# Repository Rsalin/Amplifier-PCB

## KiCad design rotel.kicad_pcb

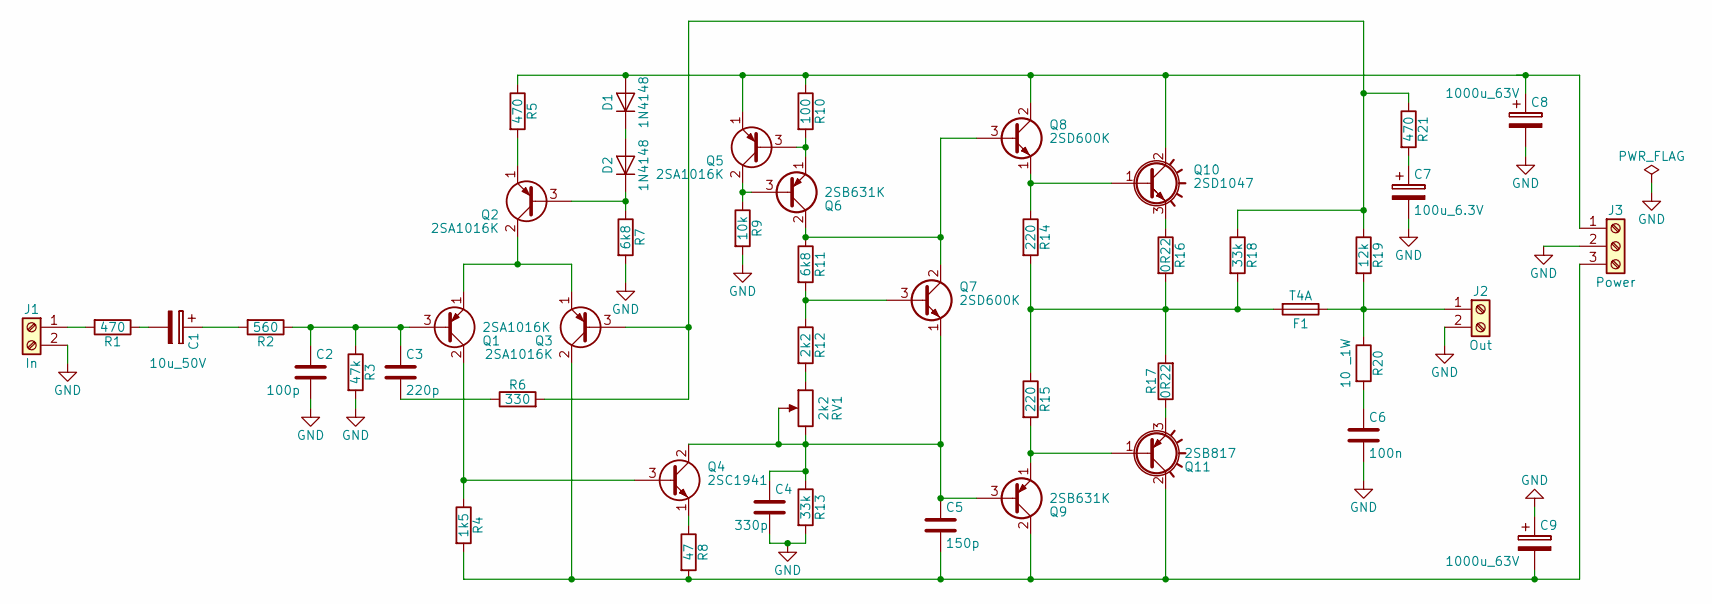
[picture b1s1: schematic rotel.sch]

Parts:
C1: 10u_50V; CP_Radial_D8.0mm_P3.80mm
C2: 100p; C_Rect_L7.0mm_W2.5mm_P5.00mm
C3: 220p; C_Rect_L7.0mm_W2.5mm_P5.00mm
C4: 330p; C_Rect_L7.0mm_W2.5mm_P5.00mm
C5: 150p; C_Rect_L7.0mm_W2.5mm_P5.00mm
C6: 100n; C_Rect_L7.0mm_W2.5mm_P5.00mm
C7: 100u_6.3V; CP_Radial_D8.0mm_P3.80mm
C8, C9: 1000u_63V; CP_Radial_D18.0mm_P7.50mm
D1, D2: 1N4148; D_DO-35_SOD27_P10.16mm_Horizontal
F1: T4A; Fuseholder5x20_horiz_SemiClosed_Casing10x25mm
J1: In; TerminalBlock_Phoenix_MKDS1.5-2pol
J2: Out; TerminalBlock_Phoenix_MKDS1.5-2pol
J3: Power; TerminalBlock_Phoenix_MKDS1.5-3pol
Q1, Q2, Q3, Q5: 2SA1016K; TO-92_Inline_Narrow_Oval
Q4: 2SC1941; TO-92_Inline_Narrow_Oval
Q6, Q9: 2SB631K; TO-126_Vertical
Q7, Q8: 2SD600K; TO-126_Vertical
Q10: 2SD1047; TO-247_TO-3P_Vertical
Q11: 2SB817; TO-247_TO-3P_Vertical
R1, R5, R21: 470; R_Axial_DIN0207_L6.3mm_D2.5mm_P10.16mm_Horizontal
R2: 560; R_Axial_DIN0207_L6.3mm_D2.5mm_P10.16mm_Horizontal
R3: 47k; R_Axial_DIN0207_L6.3mm_D2.5mm_P10.16mm_Horizontal
R4: 1k5; R_Axial_DIN0207_L6.3mm_D2.5mm_P10.16mm_Horizontal
R6: 330; R_Axial_DIN0207_L6.3mm_D2.5mm_P10.16mm_Horizontal
R7, R11: 6k8; R_Axial_DIN0207_L6.3mm_D2.5mm_P10.16mm_Horizontal
R8: 47; R_Axial_DIN0207_L6.3mm_D2.5mm_P10.16mm_Horizontal
R9: 10k; R_Axial_DIN0207_L6.3mm_D2.5mm_P10.16mm_Horizontal
R10: 100; R_Axial_DIN0207_L6.3mm_D2.5mm_P10.16mm_Horizontal
R12: 2k2; R_Axial_DIN0207_L6.3mm_D2.5mm_P10.16mm_Horizontal
R13, R18: 33k; R_Axial_DIN0207_L6.3mm_D2.5mm_P10.16mm_Horizontal
R14, R15: 220; R_Axial_DIN0207_L6.3mm_D2.5mm_P10.16mm_Horizontal
R16, R17: 0R22; R_Axial_Power_L20.0mm_W6.4mm_P7.62mm_Vertical
R19: 12k; R_Axial_DIN0207_L6.3mm_D2.5mm_P10.16mm_Horizontal
R20: 10 _1W; R_Axial_DIN0411_L9.9mm_D3.6mm_P15.24mm_Horizontal
RV1: 2k2; Potentiometer_Trimmer_ACP_CA9v_Horizontal_Px10.0mm_Py5.0mm

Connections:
GND: C2.2, C4.2, C6.2, C7.2, C8.2, C9.1, J1.2, J2.2, J3.2, R3.2, R7.2, R9.2, R13.2
unnamed: C1.1, R2.2
unnamed: C1.2, R1.1
unnamed: C2.1, C3.1, Q1.3 (B), R2.1, R3.1
unnamed: C3.2, R6.1
unnamed: C4.1, C5.1, Q4.2 (C), Q7.1 (E), Q9.3 (B), R13.1, RV1.2, RV1.3
unnamed: C5.2, C9.2, J3.3, Q3.2 (C), Q9.2 (C), Q11.2 (C), R4.2, R8.2
unnamed: C6.1, R20.2
unnamed: C7.1, R21.2
unnamed: C8.1, D1.2 (A), J3.1, Q5.1 (E), Q8.2 (C), Q10.2 (C), R5.1, R10.1
unnamed: D1.1 (K), D2.2 (A)
unnamed: D2.1 (K), Q2.3 (B), R7.1
unnamed: F1.1, J2.1, R19.2, R20.1
unnamed: F1.2, R14.2, R15.1, R16.2, R17.2, R18.2
unnamed: J1.1, R1.2
unnamed: Q1.1 (E), Q2.2 (C), Q3.1 (E)
unnamed: Q1.2 (C), Q4.3 (B), R4.1
unnamed: Q2.1 (E), R5.2
unnamed: Q3.3 (B), R6.2, R18.1, R19.1, R21.1
unnamed: Q4.1 (E), R8.1
unnamed: Q5.2 (C), Q6.3 (B), R9.1
unnamed: Q5.3 (B), Q6.1 (E), R10.2
unnamed: Q6.2 (C), Q7.2 (C), Q8.3 (B), R11.1
unnamed: Q7.3 (B), R11.2, R12.1
unnamed: Q8.1 (E), Q10.1 (B), R14.1
unnamed: Q10.3 (E), R16.1
unnamed: Q9.1 (E), Q11.1 (B), R15.2
unnamed: Q11.3 (E), R17.1
unnamed: R12.2, RV1.1

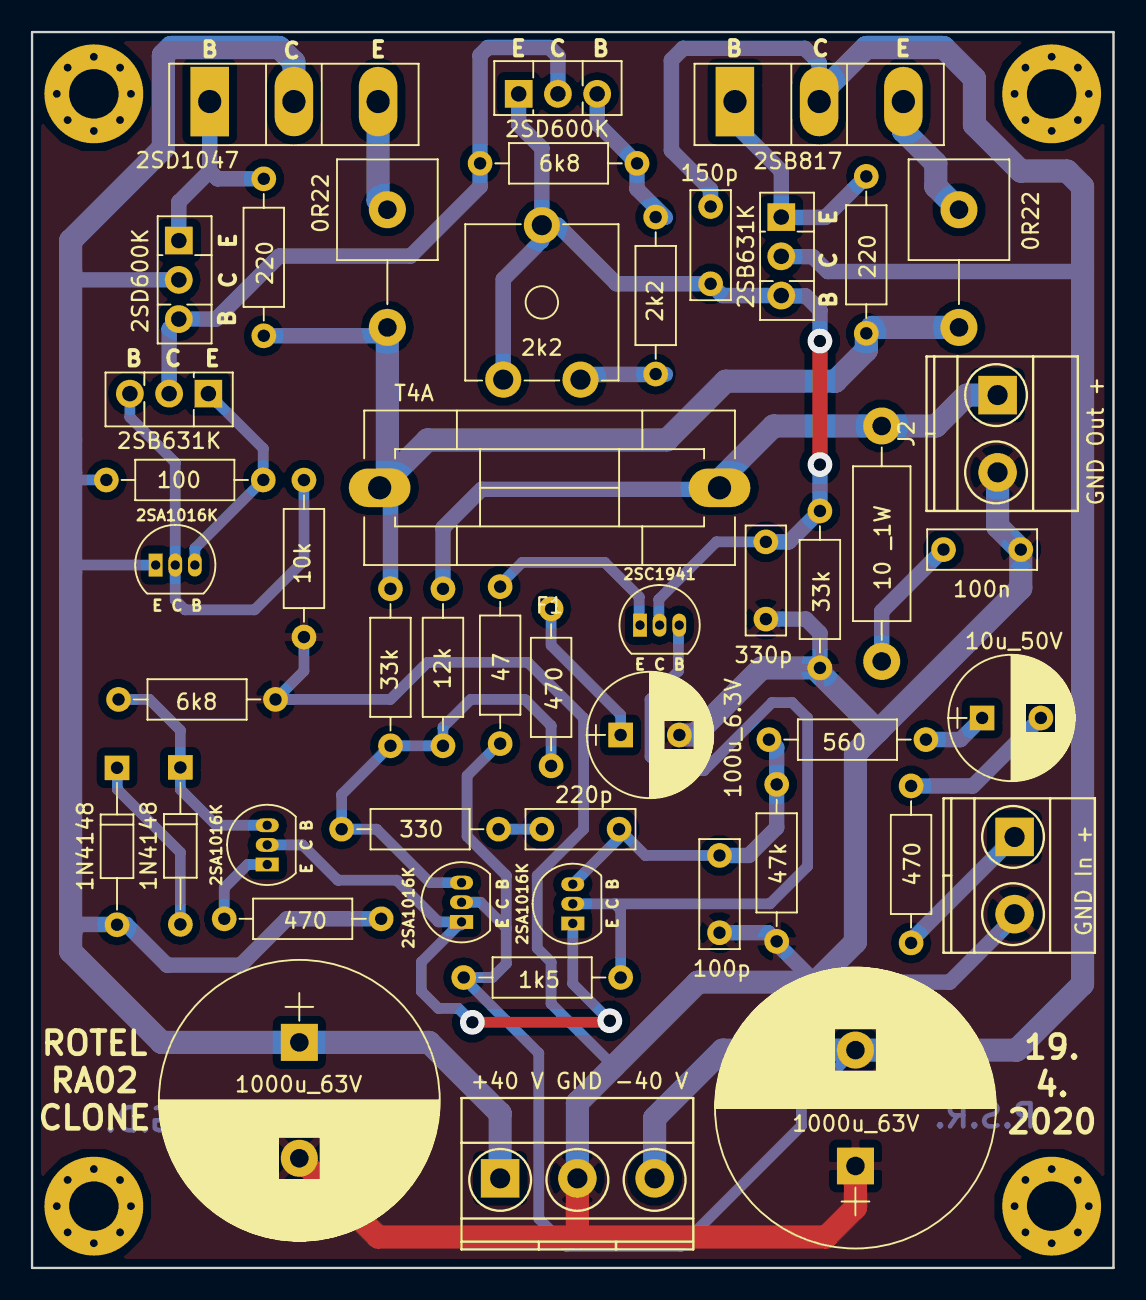
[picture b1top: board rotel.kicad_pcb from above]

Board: 2 copper layers, 70.0 x 80.0 mm, 48 parts (0 on the bottom side), 29 nets.

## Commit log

2020-03-25 Added schematic
2020-04-13 added footprints (not double checked).
2020-04-14 Exported netlist.
2020-04-14 Corrected missing footprints
2020-04-17 First PCB version. No silkscreen.
2020-04-19 Updated silkscreen layout.
2020-04-19 PCB finished.
2020-04-25 Added gerbers and BOM.
